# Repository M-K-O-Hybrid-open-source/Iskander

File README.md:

# Iskander
Iskander is an open source driver for low voltage **DC**, **BLDC**, **PMSM** motors, amde specifically for education and learning.
the repo containts some example ocodes and SIMULINK modeles to help you get started.

# Main HARDWARE
- STM32f446RE (main micro-controller)

- DRV8323H (mosfet driver and current sensors)

- CSD19534Q5A (MOSFETs)

# the hardware supports the following drives
### DC motor supported drives
- open/closed loop speed control.
- torque control.
- cascadded control.
- position control.

### BLDC motor supported drives
- open/closed loop sensored speed control (Hall effect sensors)
- sensored cascadded control.

### PMSM motor supported drives
- sensored FOC control.
- sensorless control using MRAS as speed estimator(currently under testig).
- sensorless control using EKF as speed estimator(currently under testig).

# PCB layout

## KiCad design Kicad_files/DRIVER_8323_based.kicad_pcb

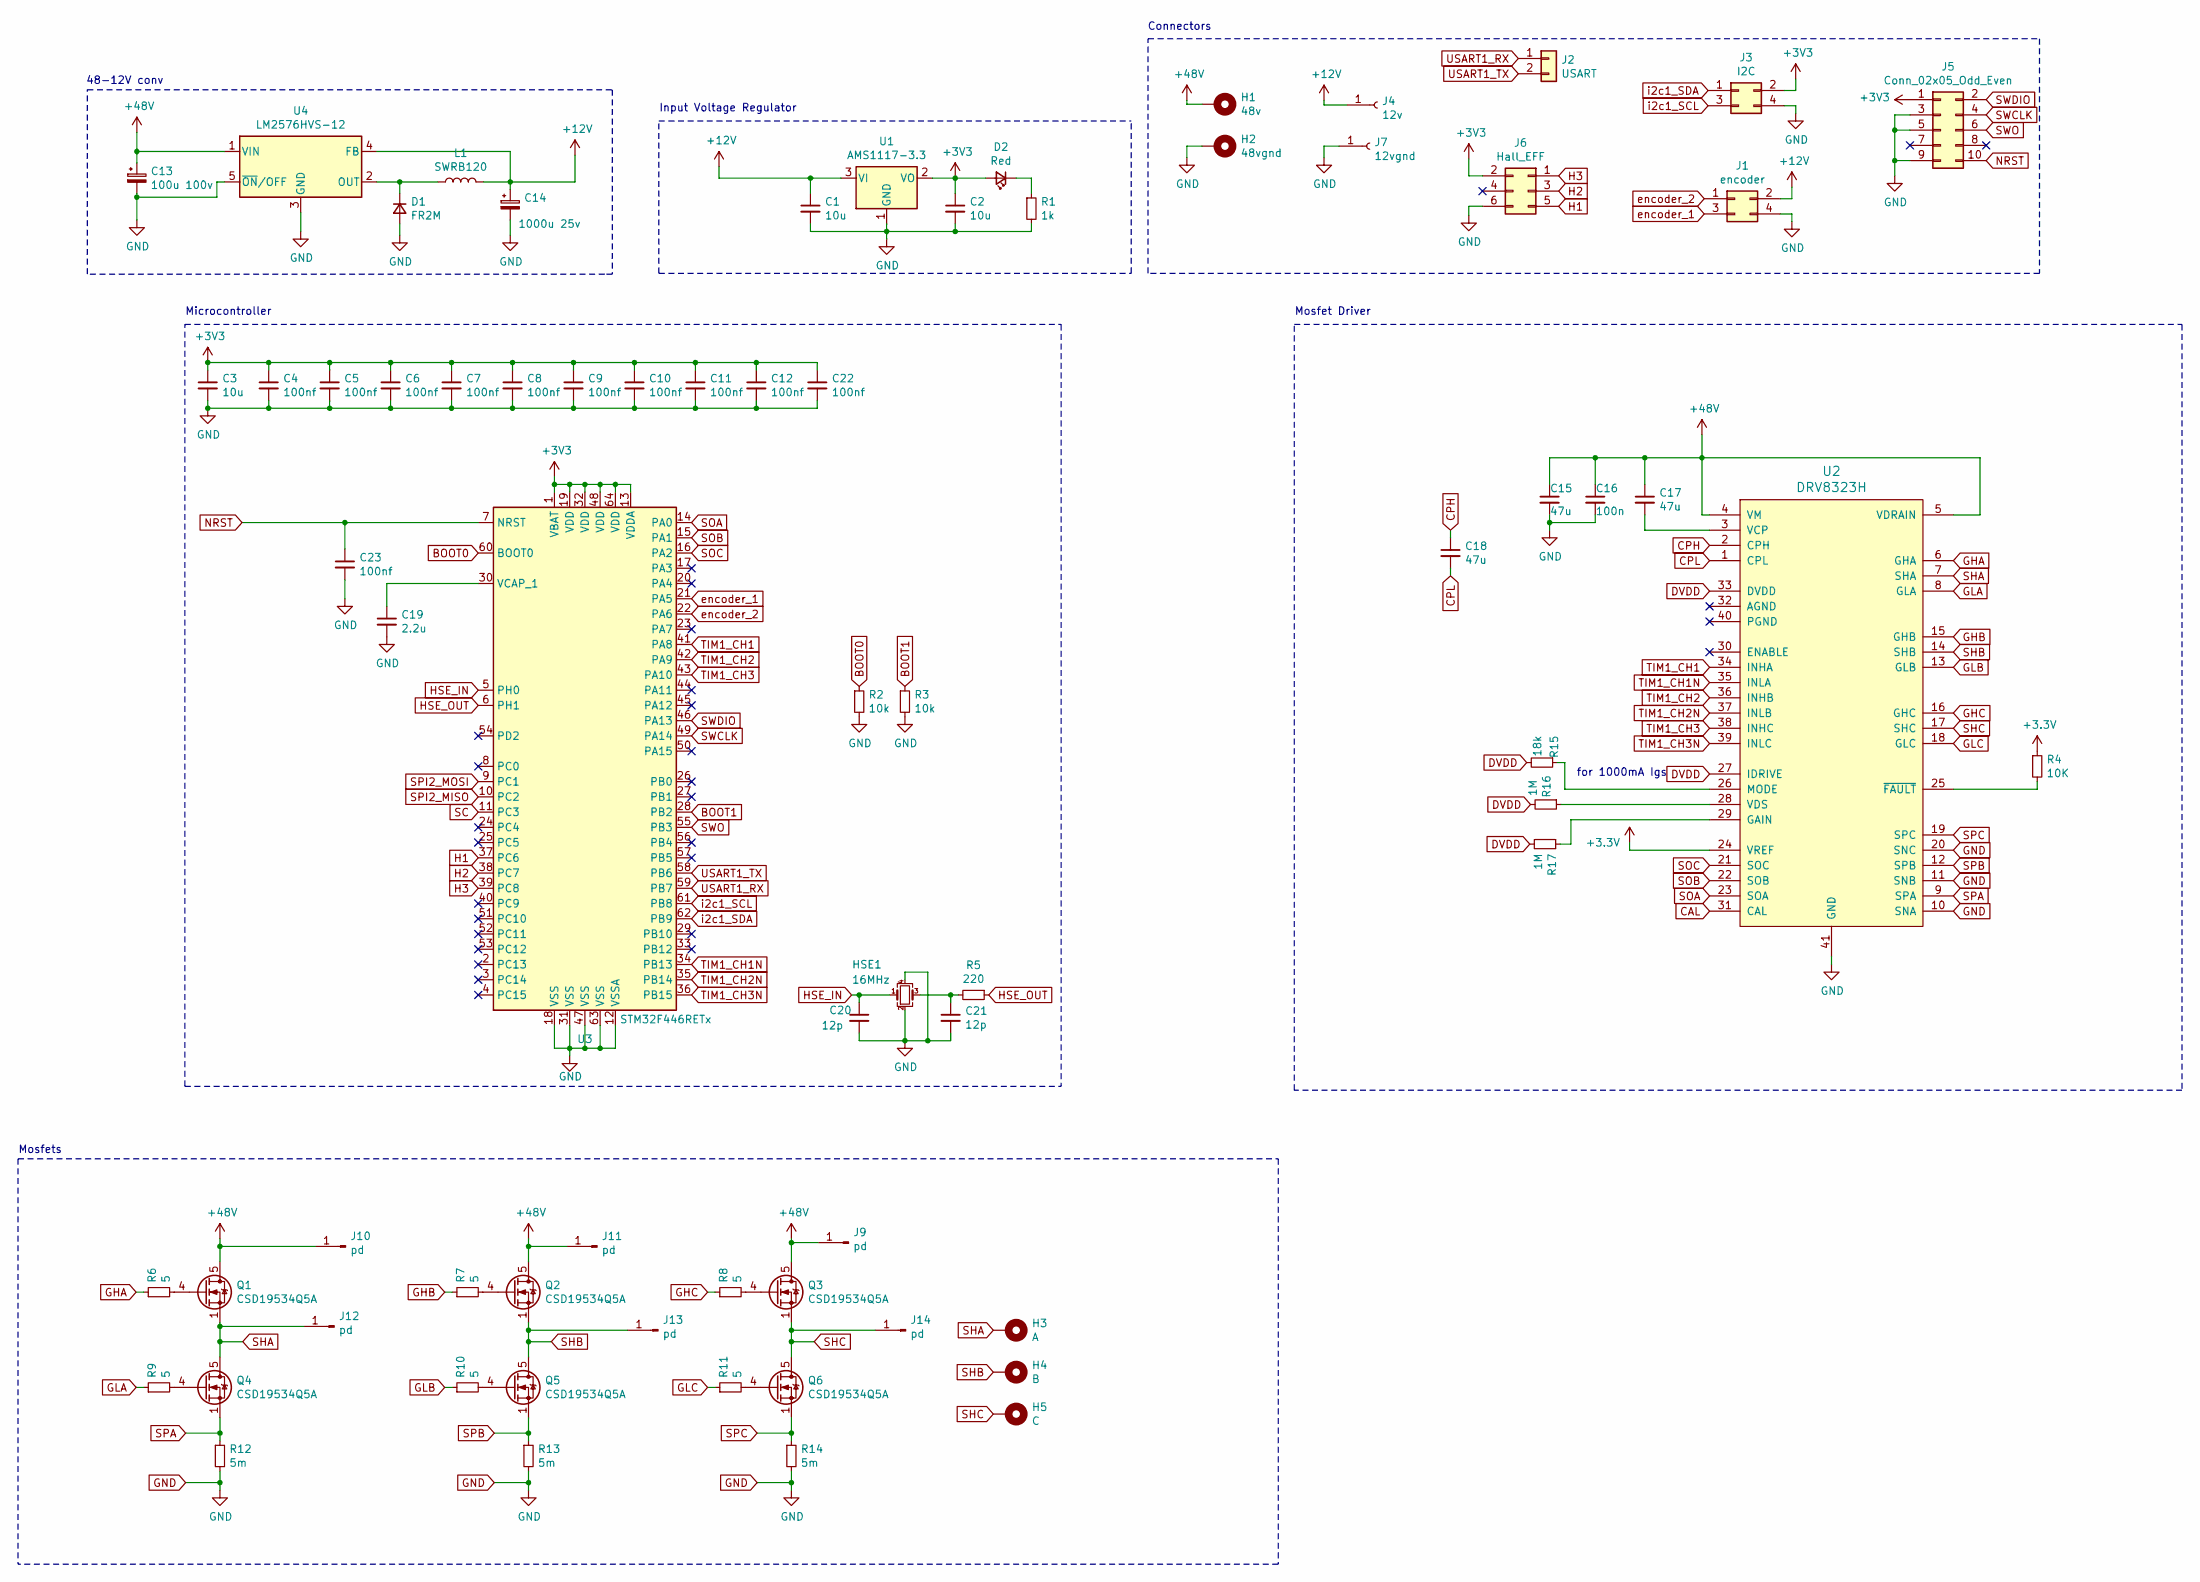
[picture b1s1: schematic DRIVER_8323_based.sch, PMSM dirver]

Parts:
C1, C2: 10u; C_0805_2012Metric
C3: 10u; C_0603_1608Metric
C4, C5, C6, C7, C8, C9, C10, C11, C12, C22, C23: 100nf; C_0402_1005Metric
C13: 100u 100v; CP_Elec_10x10
C14: 1000u 25v; CP_Elec_10x10
C15, C17, C18: 47u; C_0603_1608Metric
C16: 100n; C_0603_1608Metric
C19: 2.2u; C_0603_1608Metric
C20, C21: 12p; C_0402_1005Metric
D1: FR2M; D_SMB
D2: Red; LED_0603_1608Metric
H1: 48v; MountingHole_2.7mm_Pad
H2: 48vgnd; MountingHole_2.7mm_Pad
H3: A; MountingHole_2.7mm_Pad
H4: B; MountingHole_2.7mm_Pad
H5: C; MountingHole_2.7mm_Pad
HSE1: 16MHz; Crystal_SMD_3225-4Pin_3.2x2.5mm
J1: encoder; PinHeader_2x02_P2.54mm_Horizontal
J2: USART; PinHeader_1x02_P2.54mm_Horizontal
J3: I2C; PinHeader_2x02_P2.54mm_Horizontal
J4: 12v; SolderWirePad_1x01_SMD_1x2mm
J5: Conn_02x05_Odd_Even; PinHeader_2x05_P2.54mm_Vertical
J6: Hall_EFF; PinSocket_2x03_P2.54mm_Horizontal
J7: 12vgnd; SolderWirePad_1x01_SMD_1x2mm
J9, J10, J11, J12, J13, J14: pd; SolderWirePad_1x01_SMD_1x2mm
L1: SWRB120; L_12x12mm_H4.5mm
Q1, Q2, Q3, Q4, Q5, Q6: CSD19534Q5A; TDSON-8-1
R1: 1k; R_0603_1608Metric
R2, R3: 10k; R_0805_2012Metric
R4: 10K; R_0603_1608Metric
R5: 220; R_0603_1608Metric
R6, R7, R8, R9, R10, R11: 5; R_0805_2012Metric
R12, R13, R14: 5m; R_2512_6332Metric
R15: 18k; R_0603_1608Metric
R16, R17: 1M; R_0603_1608Metric
U1: AMS1117-3.3; SOT-223-3_TabPin2
U2: DRV8323H; QFN-40-1EP_6x6mm_P0.5mm_EP4.6x4.6mm_ThermalVias
U3: STM32F446RETx; LQFP-64_10x10mm_P0.5mm
U4: LM2576HVS-12; TO-263-5_TabPin3

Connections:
+12V: C1.1, C14.1, J1.2, J4.1, L1.2, U1.3 (VI), U4.4 (FB)
+48V: C13.1, C15.1, C16.1, C17.1, H1.1, J9.1, J10.1, J11.1, Q1.5 (D), Q2.5 (D), Q3.5 (D), U2.4 (VM), U2.5 (VDRAIN), U4.1 (VIN)
BOOT0: R2.1, U3.60 (BOOT0)
BOOT1: R3.1, U3.28 (PB2)
CAL: U2.31 (CAL)
CPH: C18.1, U2.2 (CPH)
CPL: C18.2, U2.1 (CPL)
DVDD: R15.2, R16.2, R17.2, U2.27 (IDRIVE), U2.33 (DVDD)
GHA: R6.1, U2.6 (GHA)
GHB: R7.1, U2.15 (GHB)
GHC: R8.1, U2.16 (GHC)
GLA: R9.1, U2.8 (GLA)
GLB: R10.1, U2.13 (GLB)
GLC: R11.1, U2.18 (GLC)
GND: C1.2, C2.2, C3.2, C4.2, C5.2, C6.2, C7.2, C8.2, C9.2, C10.2, C11.2, C12.2, C13.2, C14.2, C15.2, C16.2, C19.2, C20.2, C21.2, C22.2, C23.2, D1.2 (A), H2.1, HSE1.2, HSE1.4, J1.4, J3.4, J5.3, J5.5, J5.9, J6.6, J7.1, R1.2, R2.2, R3.2, R12.2, R13.2, R14.2, U1.1 (GND), U2.10 (SNA), U2.11 (SNB), U2.20 (SNC), U2.41 (GND), U3.12 (VSSA), U3.18 (VSS), U3.31 (VSS), U3.47 (VSS), U3.63 (VSS), U4.3 (GND), U4.5 (~ON~/OFF)
H1: J6.5, U3.37 (PC6)
H2: J6.3, U3.38 (PC7)
H3: J6.1, U3.39 (PC8)
HSE_IN: C20.1, HSE1.1, U3.5 (PH0)
HSE_OUT: R5.1, U3.6 (PH1)
NRST: C23.1, J5.10, U3.7 (NRST)
unnamed: C17.2, U2.3 (VCP)
unnamed: C19.1, U3.30 (VCAP_1)
unnamed: C21.1, HSE1.3, R5.2
unnamed: D1.1 (K), L1.1, U4.2 (OUT)
unnamed: D2.1 (K), R1.1
unnamed: Q1.4 (G), R6.2
unnamed: Q2.4 (G), R7.2
unnamed: Q3.4 (G), R8.2
unnamed: Q4.4 (G), R9.2
unnamed: Q5.4 (G), R10.2
unnamed: Q6.4 (G), R11.2
unnamed: R4.2, U2.25 (~FAULT)
unnamed: R15.1, U2.26 (MODE)
unnamed: R16.1, U2.28 (VDS)
unnamed: R17.1, U2.29 (GAIN)
SC: U3.11 (PC3)
SHA: H3.1, J12.1, Q1.1 (S), Q1.2 (S), Q1.3 (S), Q4.5 (D), U2.7 (SHA)
SHB: H4.1, J13.1, Q2.1 (S), Q2.2 (S), Q2.3 (S), Q5.5 (D), U2.14 (SHB)
SHC: H5.1, J14.1, Q3.1 (S), Q3.2 (S), Q3.3 (S), Q6.5 (D), U2.17 (SHC)
SOA: U2.23 (SOA), U3.14 (PA0)
SOB: U2.22 (SOB), U3.15 (PA1)
SOC: U2.21 (SOC), U3.16 (PA2)
SPA: Q4.1 (S), Q4.2 (S), Q4.3 (S), R12.1, U2.9 (SPA)
SPB: Q5.1 (S), Q5.2 (S), Q5.3 (S), R13.1, U2.12 (SPB)
SPC: Q6.1 (S), Q6.2 (S), Q6.3 (S), R14.1, U2.19 (SPC)
SPI2_MISO: U3.10 (PC2)
SPI2_MOSI: U3.9 (PC1)
SWCLK: J5.4, U3.49 (PA14)
SWDIO: J5.2, U3.46 (PA13)
SWO: J5.6, U3.55 (PB3)
TIM1_CH1: U2.34 (INHA), U3.41 (PA8)
TIM1_CH1N: U2.35 (INLA), U3.34 (PB13)
TIM1_CH2: U2.36 (INHB), U3.42 (PA9)
TIM1_CH2N: U2.37 (INLB), U3.35 (PB14)
TIM1_CH3: U2.38 (INHC), U3.43 (PA10)
TIM1_CH3N: U2.39 (INLC), U3.36 (PB15)
USART1_RX: J2.1, U3.59 (PB7)
USART1_TX: J2.2, U3.58 (PB6)
encoder_1: J1.3, U3.21 (PA5)
encoder_2: J1.1, U3.22 (PA6)
i2c1_SCL: J3.3, U3.61 (PB8)
i2c1_SDA: J3.1, U3.62 (PB9)

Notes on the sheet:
Input Voltage Regulator
Microcontroller
Connectors
Mosfet Driver
for 1000mA Igs
Mosfets
48-12V conv

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
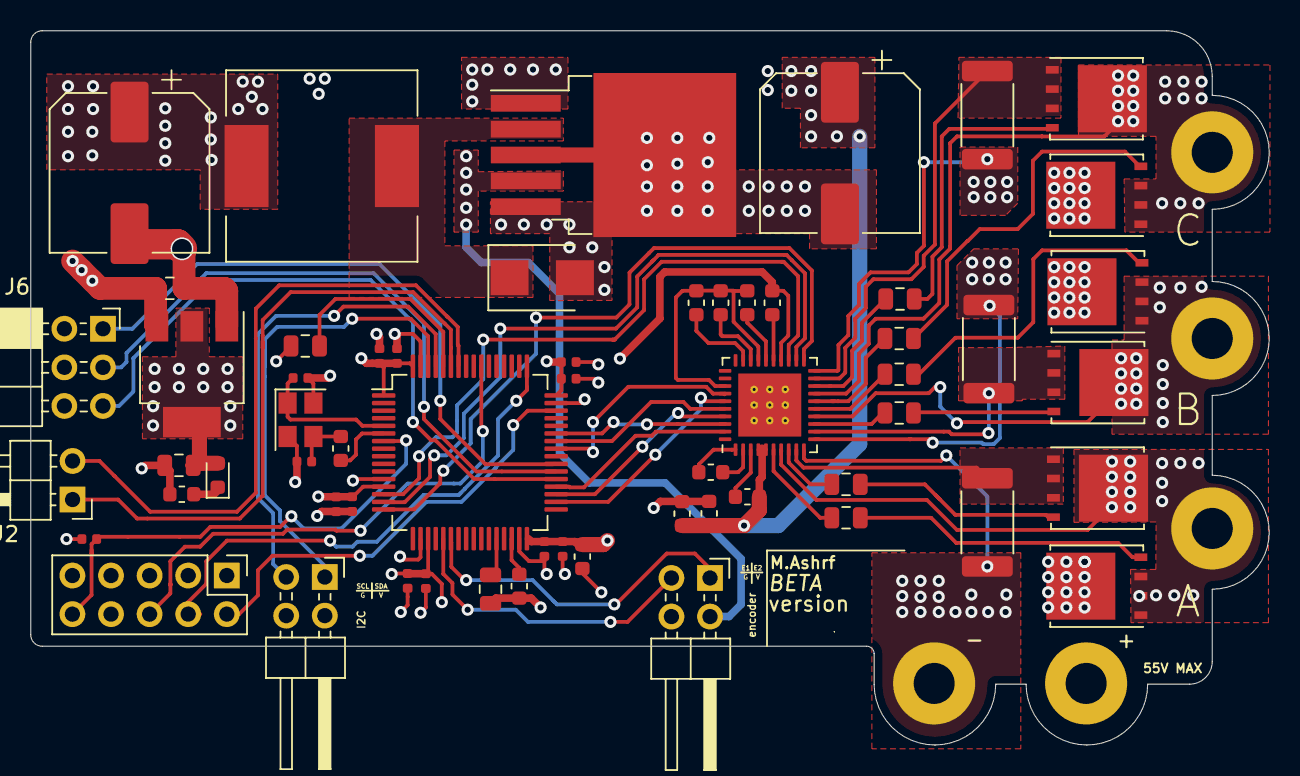
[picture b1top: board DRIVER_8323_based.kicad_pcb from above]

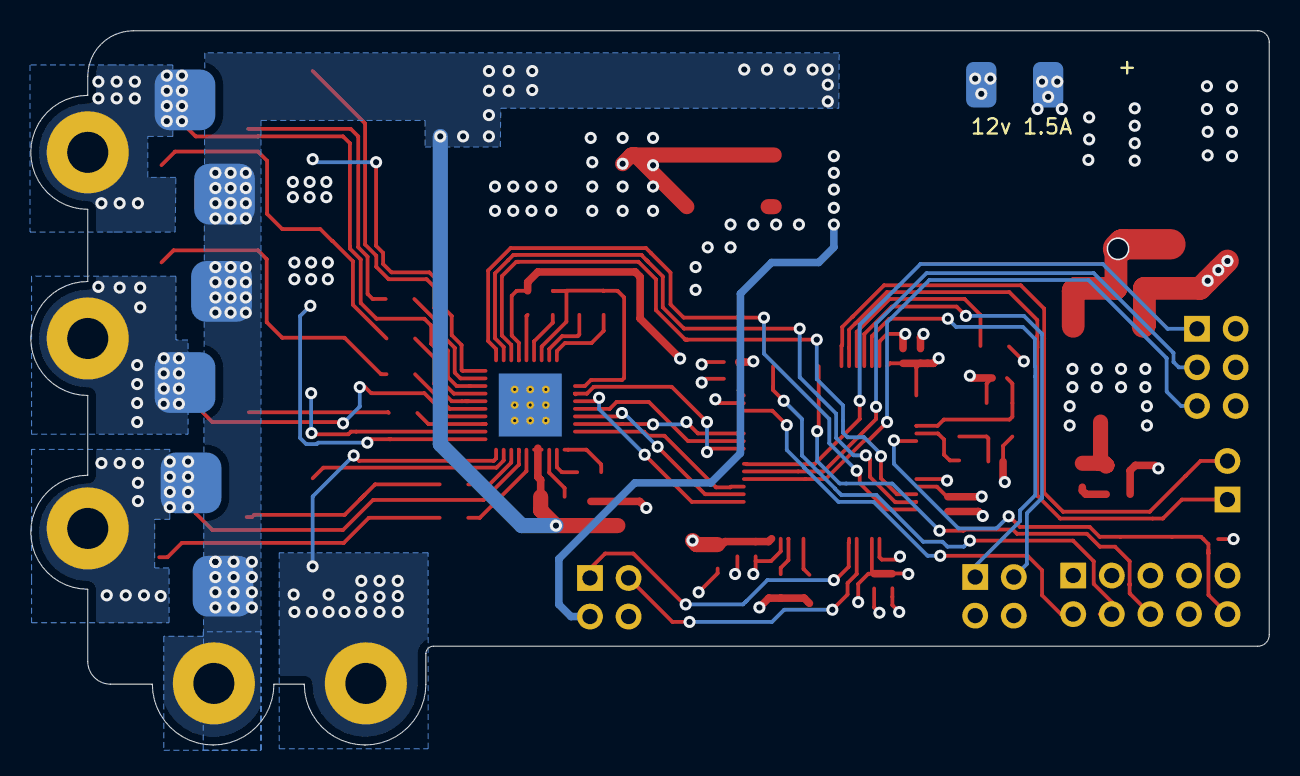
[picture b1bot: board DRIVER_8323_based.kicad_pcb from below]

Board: 4 copper layers, 81.5 x 47.0 mm, 72 parts (8 on the bottom side), 60 nets.

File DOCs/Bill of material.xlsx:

| Sourced |  | References | Value | Footprint | Quantity | Price
1 |  |  | C13 | 100u 100v | CP_Elec_10x10 | 1 | 0.0760$*5 (at least five units)
2 |  |  | C14 | 1000u 25v | CP_Elec_10x10 | 1 | 0.0760$*5 (at least five units)
3 |  |  | C4, C5, C6, C7, C8, C9, C10, C11, C12, C22, C23 | 100nf | C_0402_1005Metric | 11 | $0.0025 *11
4 |  |  | C20, C21 | 12p | C_0402_1005Metric | 2 | $0.0025 *2
5 |  |  | C15, C17, C18 | 47u | C_0603_1608Metric | 3 | $0.0025 *3
6 |  |  | C3 | 10u | C_0603_1608Metric | 1 | $0.0025*1
7 |  |  | C16 | 100n | C_0603_1608Metric | 1 | $0.0025 *1
8 |  |  | C19 | 2.2u | C_0603_1608Metric | 1 | $0.0025 *1
9 |  |  | C1, C2 | 10u | C_0805_2012Metric | 2 | $0.0025 *2
10 |  |  | R16, R17 | 1M | R_0603_1608Metric | 2 | $0.0025 *2
11 |  |  | R1 | 1k | R_0603_1608Metric | 1 | $0.0025 *1
12 |  |  | R4 | 10K | R_0603_1608Metric | 1 | $0.0025 *1
13 |  |  | R5 | 220 | R_0603_1608Metric | 1 | $0.0025 *1
14 |  |  | R15 | 18k | R_0603_1608Metric | 1 | $0.0025 *1
15 |  |  | R6, R7, R8, R9, R10, R11 | 5 | R_0805_2012Metric | 6 | $0.0025 *6
16 |  |  | R2, R3 | 10k | R_0805_2012Metric | 2 | $0.0025 *2
17 |  |  | R12, R13, R14 | 5m | R_2512_6332Metric | 3 | $0.0844 *5
18 |  |  | L1 | SWRB120 | L_12x12mm_H4.5mm | 1 | $0.2525 *1
19 |  |  | D1 | FR2M | D_SMB | 1 | $0.0796 *1
20 |  |  | D2 | Red | LED_0603_1608Metric | 1 | $0.0193 *1
21 |  |  | U3 | STM32F446RETx | LQFP-64_10x10mm_P0.5mm | 1 | $19.932 *1
22 |  |  | U2 | DRV8323H | QFN-40-1EP_6x6mm_P0.5mm_EP4.6x4.6mm_ThermalVias | 1 | $4.0804 *1
23 |  |  | U1 | AMS1117-3.3 | SOT-223-3_TabPin2 | 1 | $0.1327 *1
24 |  |  | U4 | LM2576HVS-12 | TO-263-5_TabPin3 | 1 | $1.6525 *1
25 |  |  | HSE1 | 16MHz | Crystal_SMD_3225-4Pin_3.2x2.5mm | 1 | $0.0974 *1
26 |  |  | Q1, Q2, Q3, Q4, Q5, Q6 | CSD19534Q5A | TDSON-8-1 | 6 | $1.4277 *6
27 |  |  | J2 | USART | PinHeader_1x02_P2.54mm_Horizontal | 1 | .5 EGP
28 |  |  | J1 | encoder | PinHeader_2x02_P2.54mm_Horizontal | 1 | .5EGP
29 |  |  | J3 | I2C | PinHeader_2x02_P2.54mm_Horizontal | 1 | .5EGP
30 |  |  | J5 | Conn_02x05_Odd_Even | PinHeader_2x05_P2.54mm_Vertical | 1 | 1EGP
31 |  |  | J6 | Hall_EFF | PinSocket_2x03_P2.54mm_Horizontal | 1 | 1EGP
 |  |  |  |  |  |  | Components SUM = $ 35.039
 |  |  |  |  |  |  | PCB manufacturing price = 8$

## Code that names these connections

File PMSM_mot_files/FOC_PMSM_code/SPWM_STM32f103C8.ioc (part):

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PA7.Mode=PWM Generation1 CH1 CH1N
PD1-OSC_OUT.Mode=HSE-External-Oscillator
Mcu.UserName=STM32F103C8Tx
PD0-OSC_IN.Signal=RCC_OSC_IN
PB15.Signal=GPIO_Output
RCC.SYSCLKSource=RCC_SYSCLKSOURCE_PLLCLK
PA0-WKUP.Signal=ADCx_IN0
PD1-OSC_OUT.Signal=RCC_OSC_OUT
PA13.Signal=SYS_JTMS-SWDIO
PA9.Signal=S_TIM1_CH2
PA1.Signal=ADCx_IN1
PD0-OSC_IN.Mode=HSE-External-Oscillator
PB0.Mode=PWM Generation2 CH2 CH2N
board=custom
PA14.Mode=Serial_Wire
PA8.Signal=S_TIM1_CH1
PA13.Mode=Serial_Wire
Mcu.Name=STM32F103C(8-B)Tx
PA2.Signal=ADCx_IN2
RCC.SYSCLKFreq_VALUE=72000000
Mcu.Package=LQFP48
PB1.Signal=TIM1_CH3N
PA10.Signal=S_TIM1_CH3
PA14.Signal=SYS_JTCK-SWCLK
PB1.Mode=PWM Generation3 CH3 CH3N
PB0.Signal=TIM1_CH2N
PA3.Signal=ADCx_IN3
PA7.Signal=TIM1_CH1N
